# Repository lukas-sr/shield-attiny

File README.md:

# Shield Attiny85
The actual repository is a proof of concept of an Arduino shield for ATtiny85-20PU

The main purpose of this repo is be able to do PWM quite easily with ATtiny85-20PU, alongside with Arduino

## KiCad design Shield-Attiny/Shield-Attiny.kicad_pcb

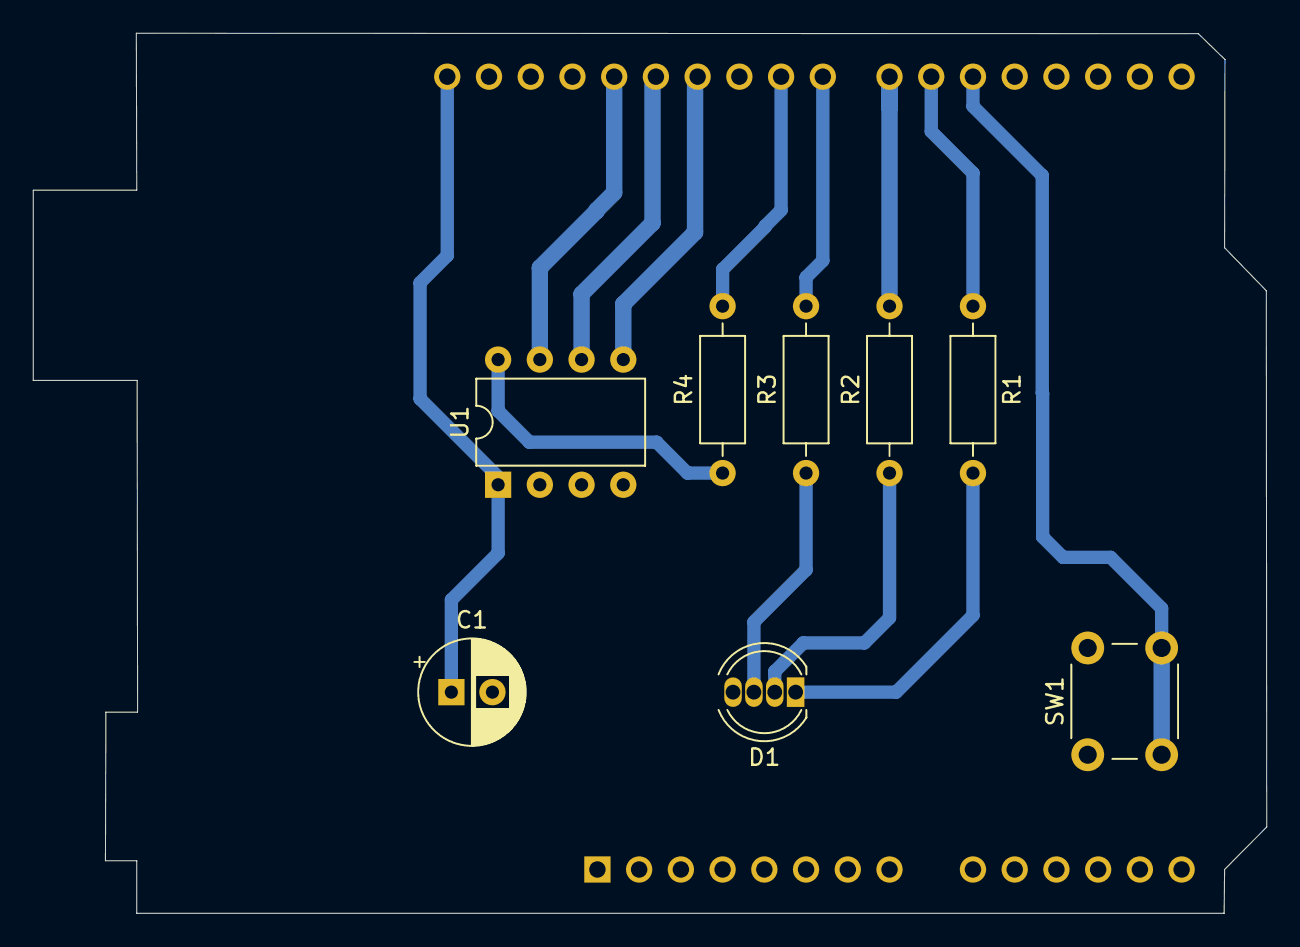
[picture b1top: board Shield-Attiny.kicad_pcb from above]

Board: 2 copper layers, 75.1 x 53.6 mm, 9 parts (1 on the bottom side), 14 nets.

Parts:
A1: Arduino_UNO_R3
C1: CP; CP_Radial_D6.3mm_P2.50mm
D1: LED_RGBC; LED_D5.0mm-4_RGB
R1, R2, R3, R4: 1k; R_Axial_DIN0207_L6.3mm_D2.5mm_P10.16mm_Horizontal
SW1: SW_Push; SW_PUSH_6mm_H7.3mm
U1: ATtiny85-20PU; DIP-8_W7.62mm

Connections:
D9: A1.24, R4.2
D10: A1.32, C1.1, U1.1
D11: A1.26, U1.5
D12: A1.27, U1.6
D13: A1.28, U1.7
GND: A1.6, A1.7, A1.29, C1.2, D1.4, SW1.1, U1.4
unnamed: A1.20, SW1.2
unnamed: A1.21, R1.1
unnamed: A1.22, R2.2
unnamed: A1.23, R3.2
unnamed: D1.1, R1.2
unnamed: D1.2, R2.1
unnamed: D1.3, R3.1
unnamed: R4.1, U1.8

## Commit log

2021-06-09 uploading in Git
2021-06-09 added images and edge cuts
2021-06-09 added .sch to main
